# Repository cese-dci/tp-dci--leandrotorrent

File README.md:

El trabajo consiste en una primera placa para el proyecto final de la CESE:
https://docs.google.com/document/d/1wCjeIKm8gcKpIWY8Q068zwM_yTZGFjd9SOWhoT_4LNc/edit?usp=sharing

El proyecto consiste en un equipo capaz de conectar dispositivos con salida de datos RS-232 o RS-485 hacia una red Ethernet. 
La placa cuenta con:
- Drivers MAX3222 e ISL83485.
- Microcontrolador MSP430F5438A .
- Memorias 24LC256 para almacenamiento de web embebida (para configuracion y monitoreo).
- Modulo WIZNET para salida de datos hacia red Ethernet.

La hoja principal del esquematico se dirige a cada una de las partes que conforman la placa, siendo estas:
- Alimentacion
- Microcontrolador
- Drivers Serie
- Memorias 
- Modulo Wiznet

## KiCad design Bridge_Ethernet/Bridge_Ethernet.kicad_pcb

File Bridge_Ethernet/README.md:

Comenzar a ver Esquemático desde el archivo "Bridge_Ethernet.sch"

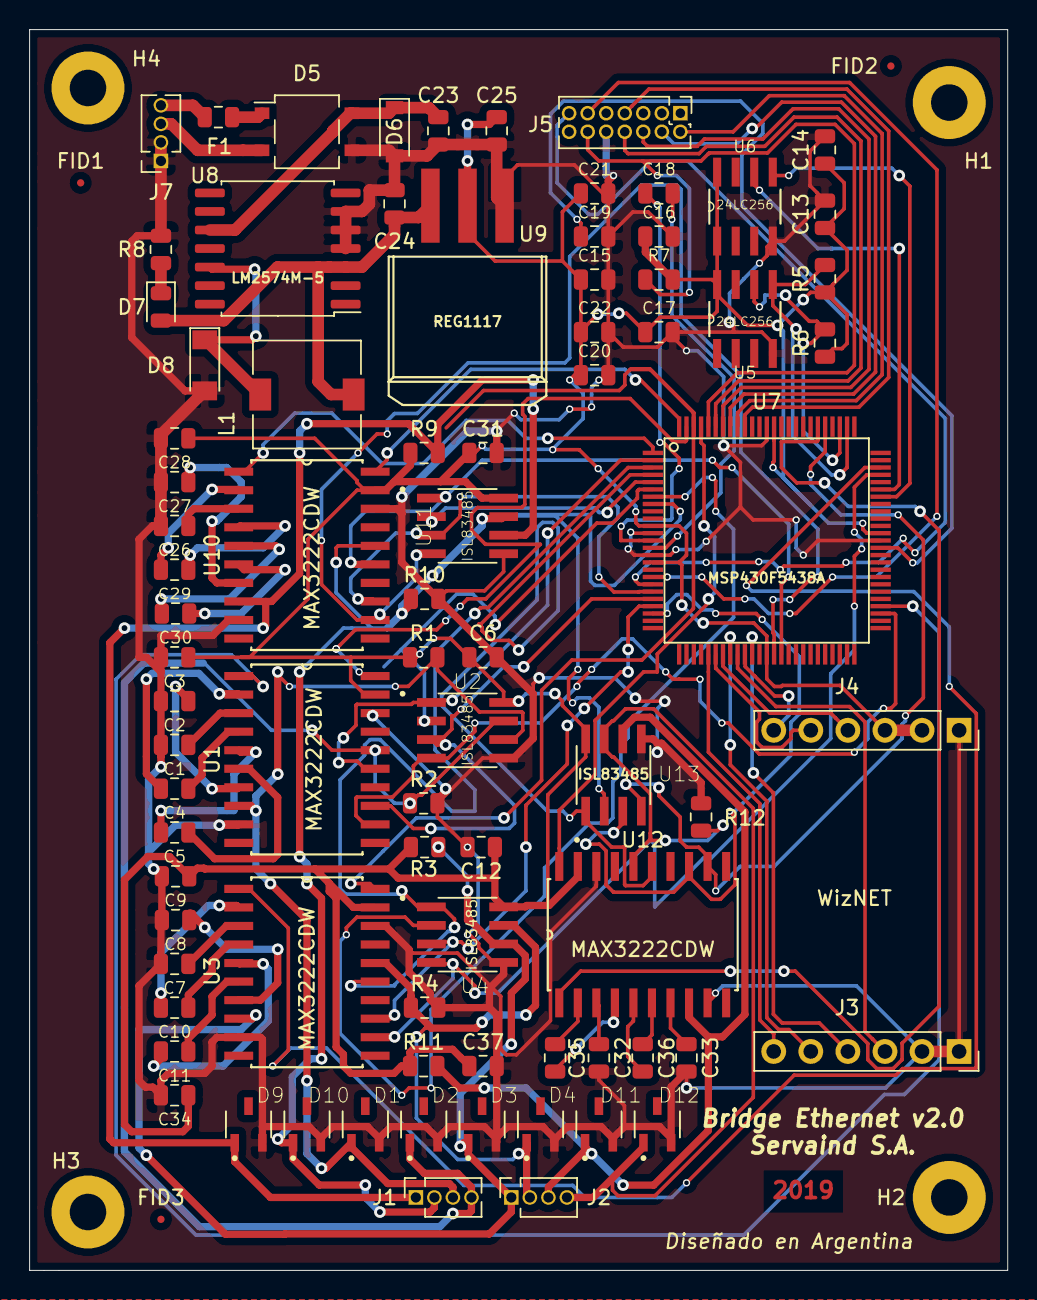
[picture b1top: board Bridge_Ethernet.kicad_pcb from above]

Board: 2 copper layers, 67.0 x 85.0 mm, 89 parts (0 on the bottom side), 87 nets.

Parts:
C1, C2, C3, C4, C5, C6, C7, C8, C9, C10, C11, C12, C13, C14, C15, C16, C17, C18, C20, C21, C22, C26, C27, C28, C29, C30, C31, C32, C33, C34, C35, C36, C37: 0.1uF; C_0805_2012Metric
C19: 470nF; C_0805_2012Metric
C23: 22uF; C_0805_2012Metric
C24: 220uF; C_0805_2012Metric
C25: 10uF; C_0805_2012Metric
D1, D2, D3, D4, D9, D10, D11, D12: GL05T-E3-08; SOT95P280X125-3N
D5: MB2S; TO-269AA
D6: BZT52BC30-7; D_SOD-123
D7: VCC_5V; LED_0805_2012Metric
D8: 10MQ060N; D_MiniMELF
F1: Polyswitch; Fuse_0805_2012Metric
FID1, FID2, FID3: Fiducial; Fiducial_0.5mm_Mask1mm
H1, H2, H3, H4: MountingHole; MountingHole_2.5mm_Pad
J1, J2: Conn_01x04_Female; PinSocket_1x04_P1.27mm_Vertical
J3, J4: Conn_01x06; PinSocket_1x06_P2.54mm_Vertical
J5: Conn_2Rows-13Pins; PinHeader_2x07_P1.27mm_Vertical
J7: Conn_01x04_Male; PinSocket_1x04_P1.27mm_Vertical
L1: 330uH; L_7.3x7.3_H4.5
R1, R2, R3, R4, R9, R10, R11, R12: 4K7; R_0805_2012Metric
R5, R6: 10K; R_0805_2012Metric
R7: 47K; R_0805_2012Metric
R8: 470; R_0805_2012Metric
U1, U3, U10, U12: MAX3222CDW; SOIC127P1032X265-20N
U2, U4, U11, U13: ISL83485; SOIC127P600X175-8N
U5, U6: 24LC256; SOIC127P600X175-8N
U7: MSP430F5438A; PZ100
U8: LM2574M-5; SOIC-14W_7.5x9mm_P1.27mm
U9: REG1117; DD-3

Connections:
+3V3: C3.1, C6.1, C9.1, C12.1, C13.1, C14.1, C15.1, C16.1, C17.1, C20.1, C21.1, C22.1, C25.1, C28.1, C31.1, C34.1, C37.1, J4.2, J4.3, R1.1, R3.1, R5.1, R6.1, R7.2, R9.1, R11.1, U1.19, U2.8, U3.19, U4.8, U5.8, U6.1, U6.8, U7.11, U7.16, U7.38, U7.64, U7.87, U9.2, U10.19, U11.8, U12.19, U13.8
+5V: C24.1, D7.2, L1.2, U8.3, U9.3
/232_0: U7.1, U10.1
/232_1: U1.15, U2.1, U7.2
/232_2: U3.15, U4.1, U7.3
/232_3: U7.4, U12.15, U13.1
/485_0: U7.5, U11.2
/485_1: U2.2, U7.6
/485_2: U4.2, U7.7
/485_3: U7.8, U13.2
/A_485_0: D9.1, J1.1, R9.2, U10.8, U11.6
/A_485_1: D1.1, J1.3, R1.2, U1.8, U2.6
/A_485_2: D3.1, J2.1, R3.2, U3.8, U4.6
/A_485_3: D11.1, J2.3, R11.2, U12.8, U13.6
/Alimentación/VCC1: F1.2, J7.4
/Alimentación/VCC2: D5.2, J7.3
/B_485_0: D10.1, J1.2, R10.1, U10.16, U11.7
/B_485_1: D2.1, J1.4, R2.1, U1.16, U2.7
/B_485_2: D4.1, J2.2, R4.1, U3.16, U4.7
/B_485_3: D12.1, J2.4, R12.1, U12.16, U13.7
/Memorias/SCL1: R6.2, U5.6, U7.78
/Memorias/SCL2: U6.6, U7.70
/Memorias/SDA1: R5.2, U5.5, U7.77
/Memorias/SDA2: U6.5, U7.69
/Microcontrolador/BSL_RX: J5.13, U7.19
/Microcontrolador/BSL_TX: J5.11, U7.18
/Microcontrolador/MICRO_RTS_1: J5.12, R7.1, U7.96
/Microcontrolador/MICRO_TCK_1: J5.8, U7.95
/Microcontrolador/MICRO_TD0_1: J5.2, U7.92
/Microcontrolador/MICRO_TDI_1: J5.4, U7.93
/Microcontrolador/MICRO_TMS_1: J5.6, U7.94
/Microcontrolador/MISO_WIZ820: J4.6, U7.35
/Microcontrolador/MOSI_WIZ820: J3.3, U7.34
/Microcontrolador/PWDN_WIZ820: J4.4, U7.32
/Microcontrolador/RESET_WIZ820: J4.5, U7.31
/Microcontrolador/SCLK_WIZ820: J3.4, U7.36
/Microcontrolador/nINT_WIZ820: J3.6, U7.30
/Microcontrolador/nSS_WIZ820: J3.5, U7.33
/RTS0: U7.20, U10.13, U11.3
/RTS1: U1.13, U2.3, U7.21
/RTS2: U3.13, U4.3, U7.22
/RTS3: U7.23, U12.13, U13.3
/RX0: U7.40, U10.15, U11.1
/RX1: U1.1, U7.54
/RX2: U3.1, U7.73
/RX3: U7.81, U12.1
/SHDN0: U7.100, U10.20
/SHDN1: U1.20, U7.99
/SHDN2: U3.20, U7.98
/SHDN3: U7.97, U12.20
/TX0: U7.39, U10.12, U11.4
/TX1: U1.12, U2.4, U7.53
/TX2: U3.12, U4.4, U7.72
/TX3: U7.80, U12.12, U13.4
GND: C1.2, C2.2, C3.2, C6.2, C7.2, C8.2, C9.2, C12.2, C13.2, C14.2, C15.2, C16.2, C17.2, C19.2, C20.2, C21.2, C22.2, C23.2, C24.2, C25.2, C26.2, C27.2, C28.2, C31.2, C32.2, C33.2, C34.2, C37.2, D1.2, D2.2, D3.2, D4.2, D5.3, D6.2, D8.2, D9.2, D10.2, D11.2, D12.2, J3.1, J3.2, J4.1, J5.10, J7.1, J7.2, R2.2, R4.2, R8.2, R10.2, R12.2, U1.9, U1.18, U2.5, U3.9, U3.18, U4.5, U5.4, U6.4, U7.12, U7.15, U7.63, U7.88, U8.4, U8.5, U8.6, U9.1, U10.9, U10.18, U11.5, U12.9, U12.18, U13.5
unnamed: C1.1, U1.3
unnamed: C2.1, U1.7
unnamed: C4.1, U1.4
unnamed: C4.2, U1.2
unnamed: C5.1, U1.6
unnamed: C5.2, U1.5
unnamed: C7.1, U3.3
unnamed: C8.1, U3.7
unnamed: C10.1, U3.4
unnamed: C10.2, U3.2
unnamed: C11.1, U3.6
unnamed: C11.2, U3.5
unnamed: C18.1, U7.13
unnamed: C18.2, U7.14
unnamed: C19.1, U7.62
unnamed: C26.1, U10.3
unnamed: C27.1, U10.7
unnamed: C29.1, U10.4
unnamed: C29.2, U10.2
unnamed: C30.1, U10.6
unnamed: C30.2, U10.5
unnamed: C32.1, U12.3
unnamed: C33.1, U12.7
unnamed: C35.1, U12.4
unnamed: C35.2, U12.2
unnamed: C36.1, U12.6
unnamed: C36.2, U12.5
unnamed: D5.1, F1.1
unnamed: D7.1, R8.1
unnamed: D8.1, L1.1, U8.12
unnamed: J5.7, U7.91
VCC: C23.1, D5.4, D6.1, U8.10

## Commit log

2019-10-30 Esquemático Finalizado
2019-10-31 Esquemático Finalizado, sin warnings. Haciendo asignaciones de footprints
2019-10-31 Esquemático Finalizado. Asignaciones Realizadas. Comienzo de PCB.
2019-11-01 Esquemático Finalizado. Asignaciones Realizadas. Componentes acomodados en PCB.
2019-11-01 Esquemático Finalizado. Asignaciones Realizadas. Componentes acomodados en PCB v2.0.
2019-11-01 Esquemático Finalizado. Asignaciones Realizadas. Reacomodamiento de componentes. Inicio de Ruteo.
2019-11-01 Esquemático Finalizado. Asignaciones Realizadas. Reacomodamiento de componentes. Ruteo en Proceso.
2019-11-08 Esquemático Finalizado. Asignaciones Realizadas. Reacomodamiento de componentes. Ruteo Finalizado.
2019-11-17 v2.0. Faltan algunos componentes 3D. Correciones relizadas.
2019-11-22 Correciones relizadas.
